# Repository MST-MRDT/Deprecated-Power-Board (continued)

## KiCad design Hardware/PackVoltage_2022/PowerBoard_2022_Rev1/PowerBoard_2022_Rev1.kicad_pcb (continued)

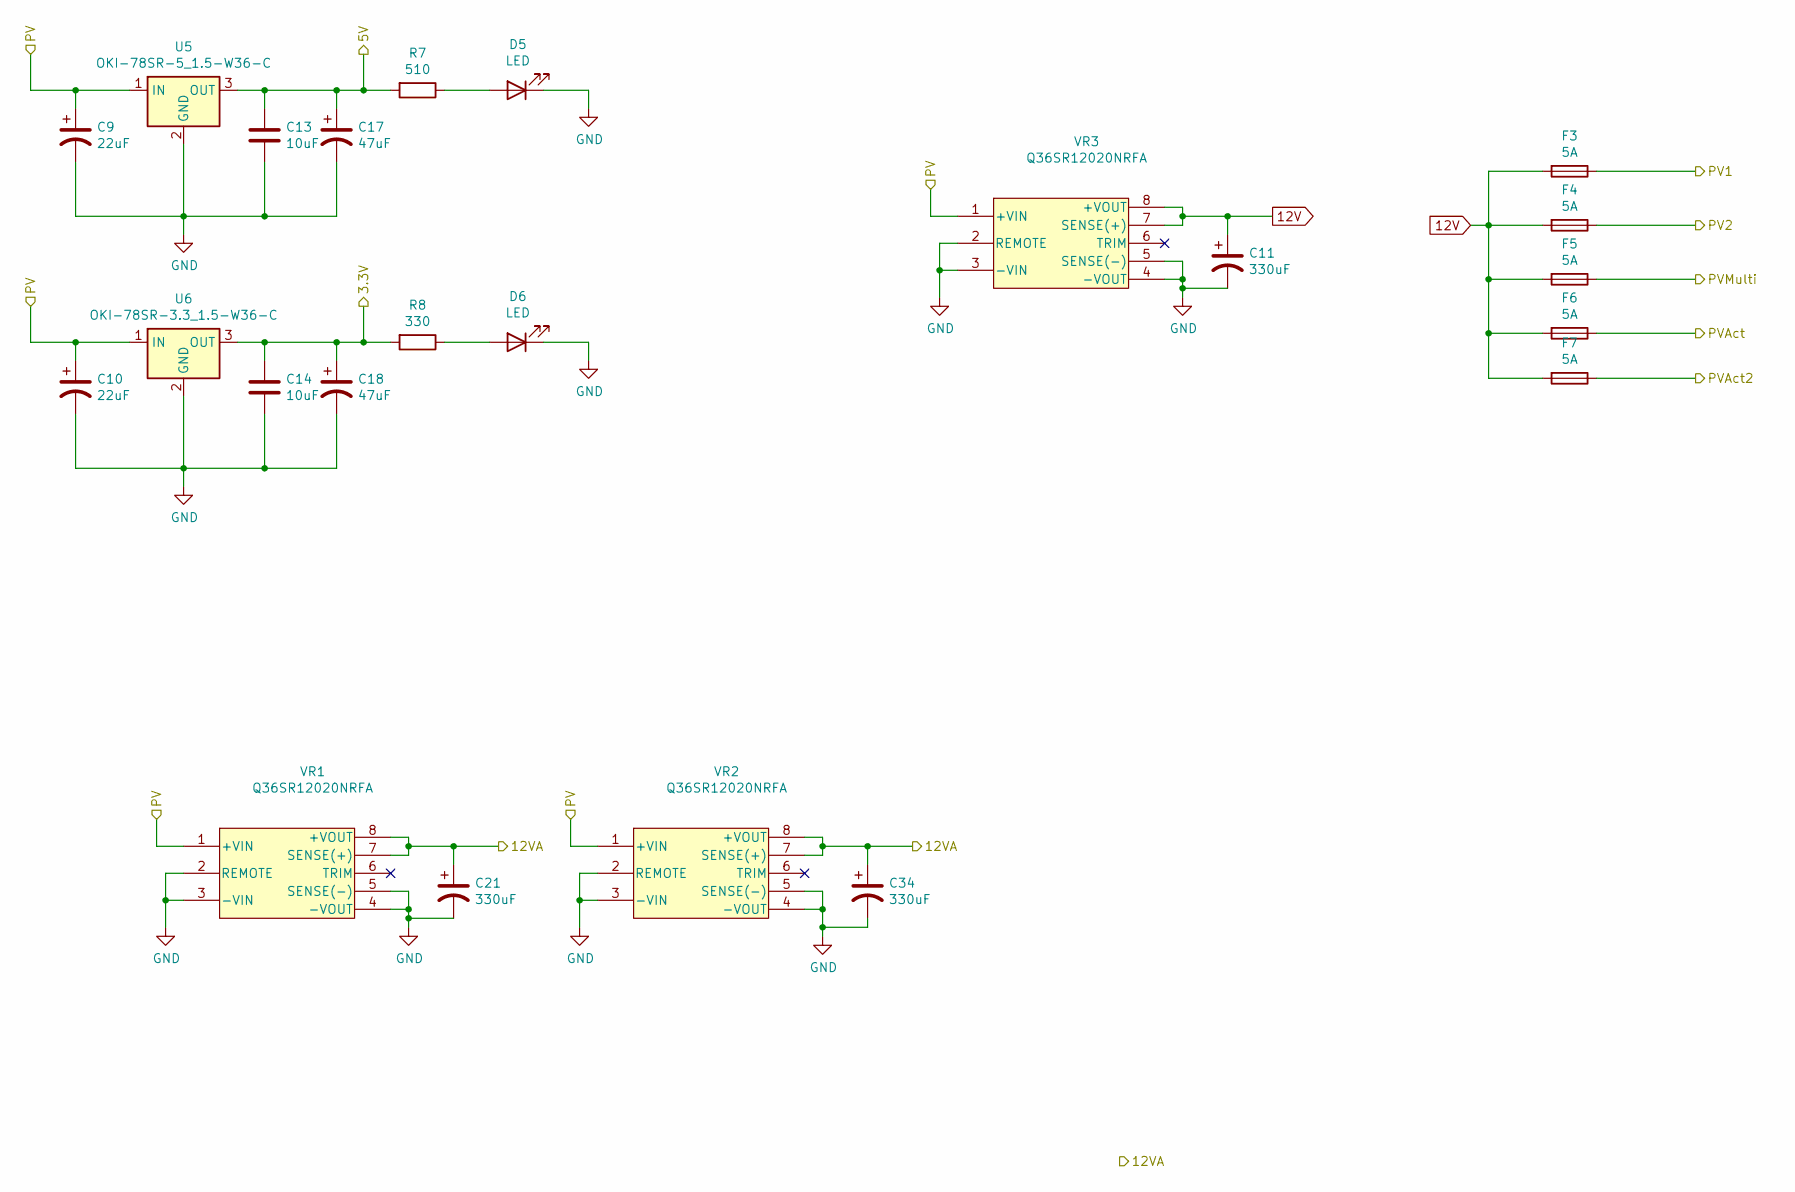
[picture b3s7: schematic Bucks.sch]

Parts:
C9, C10: 22uF; CP_Radial_D6.3mm_P2.50mm
C11, C21, C34: 330uF; CP_Radial_D12.5mm_P5.00mm
C13, C14: 10uF; C_0603_1608Metric_Pad1.05x0.95mm_HandSolder
C17, C18: 47uF; CP_Radial_D6.3mm_P2.50mm
D5, D6: LED; LED_0603_1608Metric_Pad1.05x0.95mm_HandSolder
F3, F4, F5, F6, F7: 5A; ATC_Fuse_Block
R7: 510; R_0603_1608Metric_Pad1.05x0.95mm_HandSolder
R8: 330; R_0603_1608Metric_Pad1.05x0.95mm_HandSolder
U5: OKI-78SR-5_1.5-W36-C; OKI_Horizontal
U6: OKI-78SR-3.3_1.5-W36-C; OKI_Horizontal
VR1, VR2, VR3: Q36SR12020NRFA

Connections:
3.3V: C14.1, C18.1, R8.2, U6.3 (OUT); also elsewhere on the board
5V: C13.1, C17.1, R7.2, U5.3 (OUT); also elsewhere on the board
12V: C11.1, F3.2, F4.2, F5.2, F6.2, F7.2, VR3.7 (SENSE(+)), VR3.8 (+VOUT)
12VA: C21.1, C34.1, VR1.7 (SENSE(+)), VR1.8 (+VOUT), VR2.7 (SENSE(+)), VR2.8 (+VOUT); also elsewhere on the board
GND: C9.2, C10.2, C11.2, C13.2, C14.2, C17.2, C18.2, C21.2, C34.2, D5.1 (K), D6.1 (K), U5.2 (GND), U6.2 (GND), VR1.2 (REMOTE), VR1.3 (-VIN), VR1.4 (-VOUT), VR1.5 (SENSE(-)), VR2.2 (REMOTE), VR2.3 (-VIN), VR2.4 (-VOUT), VR2.5 (SENSE(-)), VR3.2 (REMOTE), VR3.3 (-VIN), VR3.4 (-VOUT), VR3.5 (SENSE(-)); also elsewhere on the board
unnamed: D5.2 (A), R7.1
unnamed: D6.2 (A), R8.1
PV: C9.1, C10.1, U5.1 (IN), U6.1 (IN), VR1.1 (+VIN), VR2.1 (+VIN), VR3.1 (+VIN); also elsewhere on the board
PV1: F3.1; also elsewhere on the board
PV2: F4.1; also elsewhere on the board
PVAct: F6.1; also elsewhere on the board
PVAct2: F7.1; also elsewhere on the board
PVMulti: F5.1; also elsewhere on the board

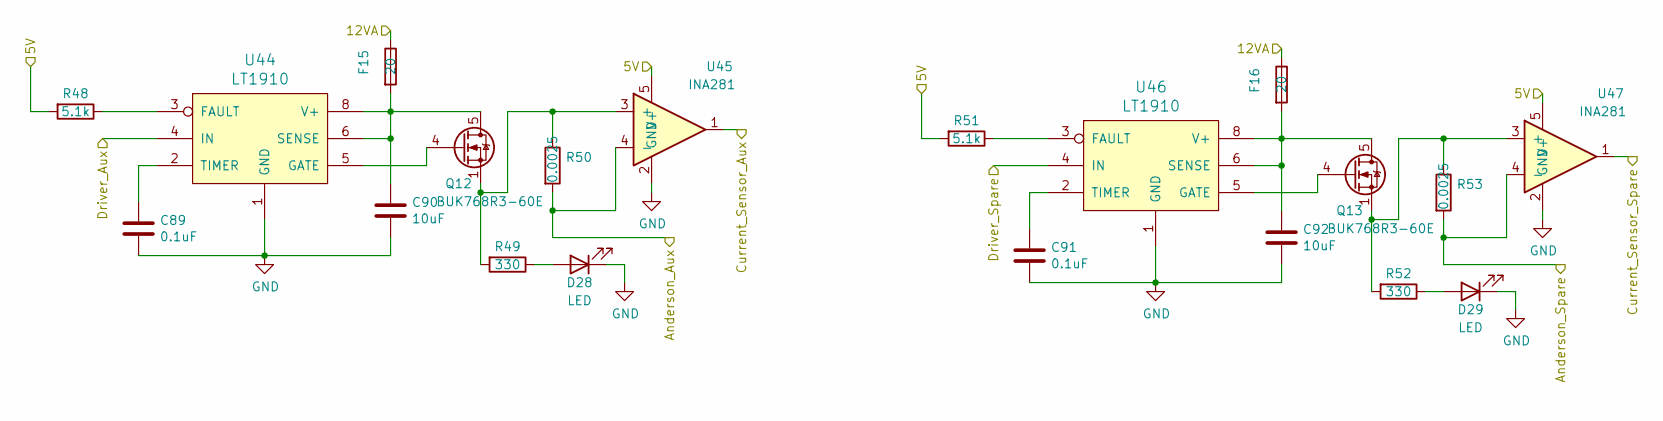
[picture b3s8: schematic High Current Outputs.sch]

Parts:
C89, C91: 0.1uF; C_0603_1608Metric_Pad1.05x0.95mm_HandSolder
C90, C92: 10uF; C_0603_1608Metric_Pad1.05x0.95mm_HandSolder
D28, D29: LED; LED_0603_1608Metric_Pad1.05x0.95mm_HandSolder
F15, F16: 20; ATC_Fuse_Block
Q12, Q13: BUK768R3-60E; LFPAK33
R48, R51: 5.1k; R_0603_1608Metric_Pad1.05x0.95mm_HandSolder
R49, R52: 330; R_0603_1608Metric_Pad1.05x0.95mm_HandSolder
R50, R53: 0.0025; R_0402_1005Metric_Pad0.72x0.64mm_HandSolder
U44, U46: LT1910; SOIC-8_3.9x4.9mm_P1.27mm
U45, U47: INA281; SOT-23-5

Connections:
5V: R48.2, R51.2, U45.5 (V+), U47.5 (V+); also elsewhere on the board
12VA: F15.1, F16.1; also elsewhere on the board
/12V/Current_Sensor_Spare: U47.1
Anderson_Aux_Logic: R50.2, U45.4 (-); also elsewhere on the board
Anderson_Spare: R53.2, U47.4 (-); also elsewhere on the board
Current_Sensor_Aux_Logic: U45.1; also elsewhere on the board
Driver_Aux_Logic: U44.4 (IN); also elsewhere on the board
Driver_Spare: U46.4 (IN); also elsewhere on the board
GND: C89.2, C90.2, C91.2, C92.2, D28.1 (K), D29.1 (K), U44.1 (GND), U45.2 (GND), U46.1 (GND), U47.2 (GND); also elsewhere on the board
unnamed: C89.1, U44.2 (TIMER)
unnamed: C90.1, F15.2, Q12.5 (D), U44.6 (SENSE), U44.8 (V+)
unnamed: C91.1, U46.2 (TIMER)
unnamed: C92.1, F16.2, Q13.5 (D), U46.6 (SENSE), U46.8 (V+)
unnamed: D28.2 (A), R49.1
unnamed: D29.2 (A), R52.1
unnamed: Q12.1 (S), Q12.2 (S), Q12.3 (S), R49.2, R50.1, U45.3 (+)
unnamed: Q12.4 (G), U44.5 (GATE)
unnamed: Q13.1 (S), Q13.2 (S), Q13.3 (S), R52.2, R53.1, U47.3 (+)
unnamed: Q13.4 (G), U46.5 (GATE)
unnamed: R48.1, U44.3 (FAULT)
unnamed: R51.1, U46.3 (FAULT)

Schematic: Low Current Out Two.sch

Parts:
C93, C94, C95, C96, C102, C104, C105, C106, C107: 0.1uF; C_0603_1608Metric_Pad1.05x0.95mm_HandSolder
C97, C98, C99, C100, C101, C103, C108, C109, C110: 10uF; C_0603_1608Metric_Pad1.05x0.95mm_HandSolder
D30, D31, D32, D33, D34, D35, D36, D37, D38: LED; LED_0603_1608Metric_Pad1.05x0.95mm_HandSolder
Q14, Q15, Q16, Q17, Q18, Q19, Q20, Q21, Q22: BUK768R3-60E; LFPAK33
R54, R55, R56, R57, R66, R69, R72, R73, R74: 5.1k; R_0603_1608Metric_Pad1.05x0.95mm_HandSolder
R58, R59, R60, R61, R68, R71, R75, R76, R77: 330; R_0603_1608Metric_Pad1.05x0.95mm_HandSolder
R62, R63, R64, R65, R67, R70, R78, R79, R80: 0.0025; R_2512_6332Metric_Pad1.40x3.35mm_HandSolder
U48, U49, U50, U51, U57, U59, U60, U61, U62: LT1910; SOIC-8_3.9x4.9mm_P1.27mm
U52, U53, U54, U55, U56, U58, U63, U64, U65: INA281; SOT-23-5

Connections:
5V: R54.2, R55.2, R56.2, R57.2, R66.2, R69.2, R72.2, R73.2, R74.2, U52.5 (V+), U53.5 (V+), U54.5 (V+), U55.5 (V+), U56.5 (V+), U58.5 (V+), U63.5 (V+), U64.5 (V+), U65.5 (V+); also elsewhere on the board
Anderson_BBB: R64.2, U54.4 (-); also elsewhere on the board
Anderson_Cam1: R65.2, U55.4 (-); also elsewhere on the board
Anderson_Cam2: R63.2, U53.4 (-); also elsewhere on the board
Anderson_Drive: R67.2, U56.4 (-); also elsewhere on the board
Anderson_Gimbal: R62.2, U52.4 (-); also elsewhere on the board
Anderson_Multimedia: R70.2, U58.4 (-); also elsewhere on the board
Anderson_Nav: R78.2, U63.4 (-); also elsewhere on the board
Anderson_NetSwitch: R79.2, U64.4 (-); also elsewhere on the board
Anderson_SciSensor: R80.2, U65.4 (-); also elsewhere on the board
Current_Sensor_BBB: U54.1; also elsewhere on the board
Current_Sensor_Cam1: U55.1; also elsewhere on the board
Current_Sensor_Cam2: U53.1; also elsewhere on the board
Current_Sensor_Drive: U56.1; also elsewhere on the board
Current_Sensor_Gimbal: U52.1
Current_Sensor_Multimedia: U58.1; also elsewhere on the board
Current_Sensor_Nav: U63.1; also elsewhere on the board
Current_Sensor_NetSwitch: U64.1; also elsewhere on the board
Current_Sensor_SciSensor: U65.1
Driver_BBB: U50.4 (IN); also elsewhere on the board
Driver_Cam1: U51.4 (IN); also elsewhere on the board
Driver_Cam2: U49.4 (IN); also elsewhere on the board
Driver_Drive: U57.4 (IN); also elsewhere on the board
Driver_Gimbal: U48.4 (IN); also elsewhere on the board
Driver_Multimedia: U59.4 (IN); also elsewhere on the board
Driver_Nav: U60.4 (IN); also elsewhere on the board
Driver_NetSwitch: U61.4 (IN); also elsewhere on the board
Driver_SciSensor: U62.4 (IN); also elsewhere on the board
GND: C93.2, C94.2, C95.2, C96.2, C97.2, C98.2, C99.2, C100.2, C101.2, C102.2, C103.2, C104.2, C105.2, C106.2, C107.2, C108.2, C109.2, C110.2, D30.1 (K), D31.1 (K), D32.1 (K), D33.1 (K), D34.1 (K), D35.1 (K), D36.1 (K), D37.1 (K), D38.1 (K), U48.1 (GND), U49.1 (GND), U50.1 (GND), U51.1 (GND), U52.2 (GND), U53.2 (GND), U54.2 (GND), U55.2 (GND), U56.2 (GND), U57.1 (GND), U58.2 (GND), U59.1 (GND), U60.1 (GND), U61.1 (GND), U62.1 (GND), U63.2 (GND), U64.2 (GND), U65.2 (GND); also elsewhere on the board
unnamed: C93.1, U48.2 (TIMER)
unnamed: C94.1, U49.2 (TIMER)
unnamed: C95.1, U50.2 (TIMER)
unnamed: C96.1, U51.2 (TIMER)
unnamed: C102.1, U57.2 (TIMER)
unnamed: C104.1, U59.2 (TIMER)
unnamed: C105.1, U60.2 (TIMER)
unnamed: C106.1, U61.2 (TIMER)
unnamed: C107.1, U62.2 (TIMER)
unnamed: D30.2 (A), R58.1
unnamed: D31.2 (A), R59.1
unnamed: D32.2 (A), R60.1
unnamed: D33.2 (A), R61.1
unnamed: D34.2 (A), R68.1
unnamed: D35.2 (A), R71.1
unnamed: D36.2 (A), R75.1
unnamed: D37.2 (A), R76.1
unnamed: D38.2 (A), R77.1
unnamed: Q14.1 (S), Q14.2 (S), Q14.3 (S), R58.2, R62.1, U52.3 (+)
unnamed: Q14.4 (G), U48.5 (GATE)
unnamed: Q15.1 (S), Q15.2 (S), Q15.3 (S), R59.2, R63.1, U53.3 (+)
unnamed: Q15.4 (G), U49.5 (GATE)
unnamed: Q16.1 (S), Q16.2 (S), Q16.3 (S), R60.2, R64.1, U54.3 (+)
unnamed: Q16.4 (G), U50.5 (GATE)
unnamed: Q17.1 (S), Q17.2 (S), Q17.3 (S), R61.2, R65.1, U55.3 (+)
unnamed: Q17.4 (G), U51.5 (GATE)
unnamed: Q18.1 (S), Q18.2 (S), Q18.3 (S), R67.1, R68.2, U56.3 (+)
unnamed: Q18.4 (G), U57.5 (GATE)
unnamed: Q19.1 (S), Q19.2 (S), Q19.3 (S), R70.1, R71.2, U58.3 (+)
unnamed: Q19.4 (G), U59.5 (GATE)
unnamed: Q20.1 (S), Q20.2 (S), Q20.3 (S), R75.2, R78.1, U63.3 (+)
unnamed: Q20.4 (G), U60.5 (GATE)
unnamed: Q21.1 (S), Q21.2 (S), Q21.3 (S), R76.2, R79.1, U64.3 (+)
unnamed: Q21.4 (G), U61.5 (GATE)
unnamed: Q22.1 (S), Q22.2 (S), Q22.3 (S), R77.2, R80.1, U65.3 (+)
unnamed: Q22.4 (G), U62.5 (GATE)
unnamed: R54.1, U48.3 (FAULT)
unnamed: R55.1, U49.3 (FAULT)
unnamed: R56.1, U50.3 (FAULT)
unnamed: R57.1, U51.3 (FAULT)
unnamed: R66.1, U57.3 (FAULT)
unnamed: R69.1, U59.3 (FAULT)
unnamed: R72.1, U60.3 (FAULT)
unnamed: R73.1, U61.3 (FAULT)
unnamed: R74.1, U62.3 (FAULT)
PV1: C98.1, C99.1, C100.1, C108.1, Q15.5 (D), Q16.5 (D), Q17.5 (D), Q20.5 (D), U49.6 (SENSE), U49.8 (V+), U50.6 (SENSE), U50.8 (V+), U51.6 (SENSE), U51.8 (V+), U60.6 (SENSE), U60.8 (V+); also elsewhere on the board
PV2: C97.1, C101.1, C109.1, C110.1, Q14.5 (D), Q18.5 (D), Q21.5 (D), Q22.5 (D), U48.6 (SENSE), U48.8 (V+), U57.6 (SENSE), U57.8 (V+), U61.6 (SENSE), U61.8 (V+), U62.6 (SENSE), U62.8 (V+); also elsewhere on the board
PVMulti: C103.1, Q19.5 (D), U59.6 (SENSE), U59.8 (V+); also elsewhere on the board

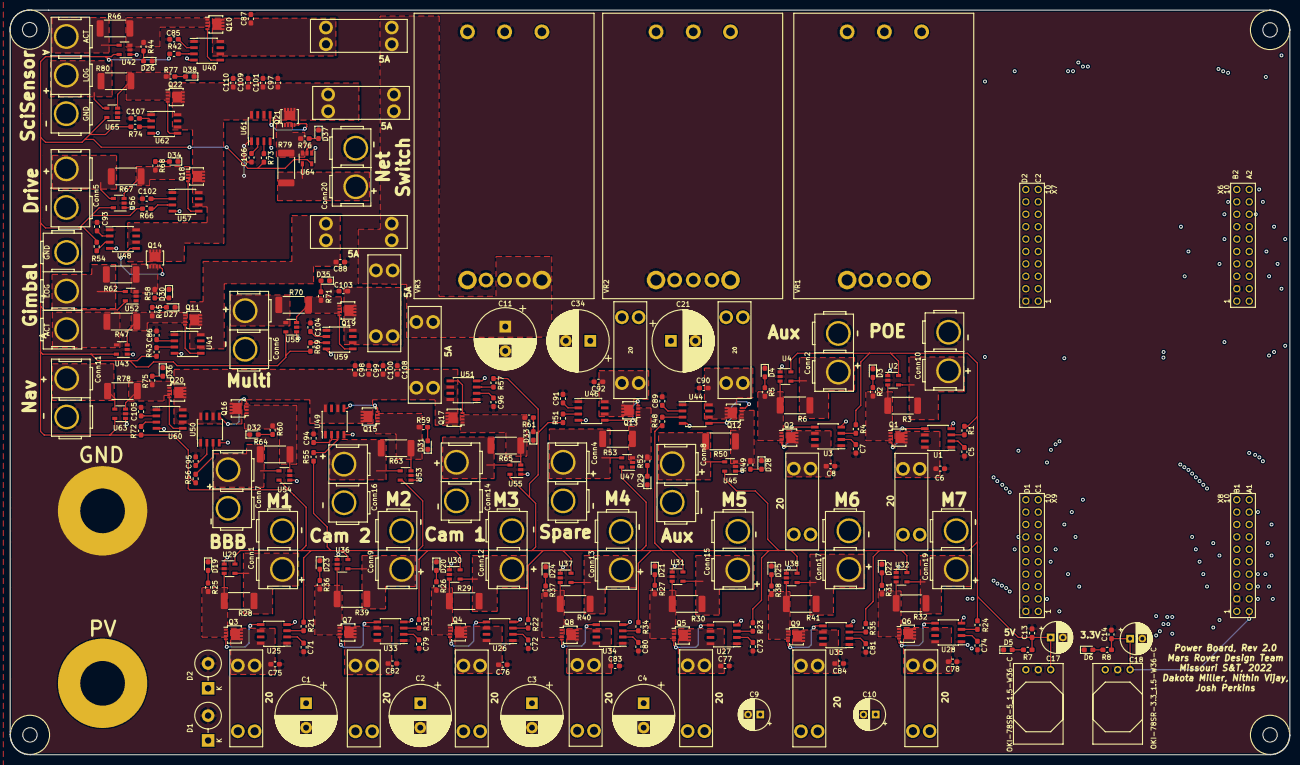
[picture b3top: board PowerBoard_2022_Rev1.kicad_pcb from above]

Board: 4 copper layers, 261.9 x 152.4 mm, 261 parts (0 on the bottom side), 197 nets.

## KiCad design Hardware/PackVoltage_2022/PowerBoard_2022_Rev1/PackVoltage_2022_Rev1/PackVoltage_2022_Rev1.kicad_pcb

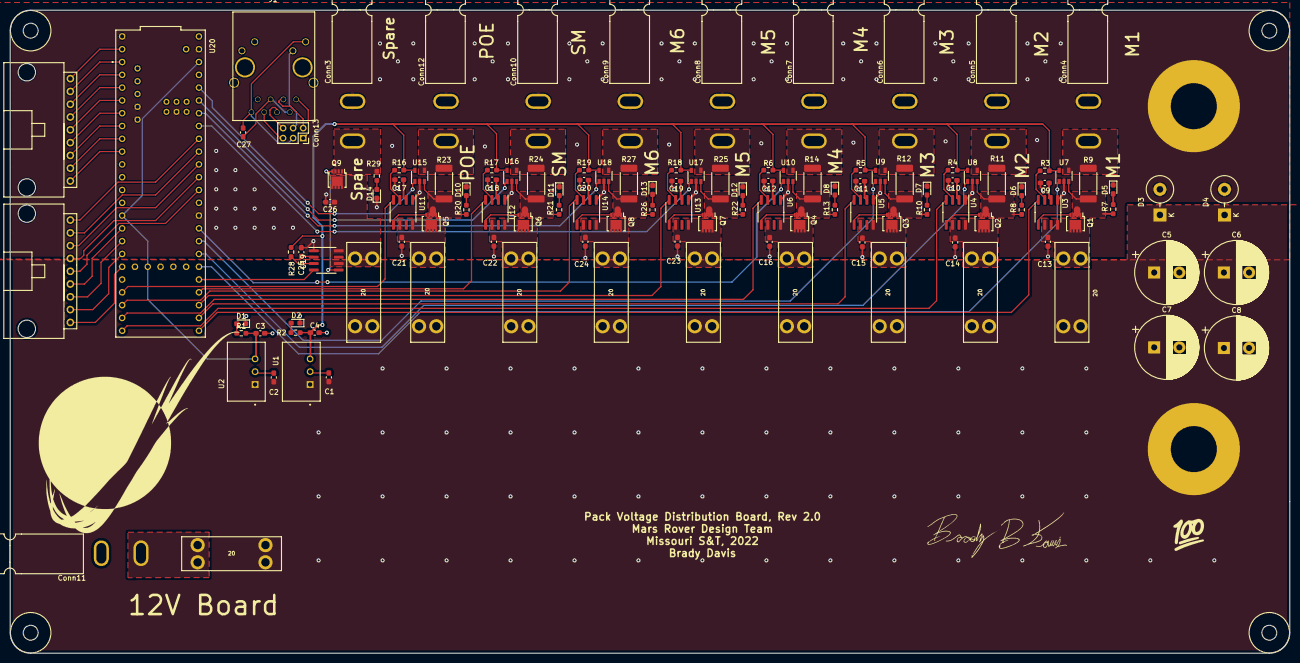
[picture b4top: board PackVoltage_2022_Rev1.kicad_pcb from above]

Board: 2 copper layers, 254.0 x 127.6 mm, 123 parts (0 on the bottom side), 111 nets.

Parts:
C1, C2, C13, C14, C15, C16, C21, C22, C23, C24, C26: 10uF; C_0603_1608Metric_Pad1.08x0.95mm_HandSolder
C3, C4: 22uF; C_0603_1608Metric_Pad1.08x0.95mm_HandSolder
C5, C6, C7, C8: 470uF; CP_Radial_D12.5mm_P5.00mm
C9, C10, C11, C12, C17, C18, C19, C20, C25: 0.1uF; C_0603_1608Metric_Pad1.08x0.95mm_HandSolder
C27: 0.1 uF; C_0603_1608Metric_Pad1.08x0.95mm_HandSolder
Conn1, Conn2: Molex_SL_10; MOLEX_SL_09_Horizontal
Conn3: Spare; Square_Anderson_2_H_Stacked_PV
Conn4: M1; Square_Anderson_2_H_Stacked_PV
Conn5: M2; Square_Anderson_2_H_Stacked_PV
Conn6: M3; Square_Anderson_2_H_Stacked_PV
Conn7: M4; Square_Anderson_2_H_Stacked_PV
Conn8: M5; Square_Anderson_2_H_Stacked_PV
Conn9: M6; Square_Anderson_2_H_Stacked_PV
Conn10: SpareMotor; Square_Anderson_2_H_Stacked_PV
Conn11: 12V; Square_Anderson_2_H_Stacked_PV
Conn12: POE; Square_Anderson_2_H_Stacked_PV
Conn13: Molex_uF_D_06; PinSocket_2x03_P2.00mm_Vertical
D1, D2, D5, D6, D7, D8, D10, D11, D12, D13, D14: LED; LED_0603_1608Metric_Pad1.05x0.95mm_HandSolder
D3, D4: 1.5KE36A+; D_DO-201_P5.08mm_Vertical_KathodeUp
F1, F2, F3, F4, F5, F6, F7, F8, F9, F10: 20; ATC_Fuse_Block
GND1: Via; BATT_PWR_VIA
J1: RJ45_LED_Shielded; RJ45_Teensy
Q1, Q2, Q3, Q4, Q5, Q6, Q7, Q8, Q9: BUK7S2R0-40HJ; LFPAK33
R1: 130; R_0603_1608Metric_Pad0.98x0.95mm_HandSolder
R2: 300; R_0603_1608Metric_Pad0.98x0.95mm_HandSolder
R3, R4, R5, R6, R16, R17, R18, R19, R28: 5.1k; R_0603_1608Metric_Pad0.98x0.95mm_HandSolder
R7, R8, R10, R13, R20, R21, R22, R26, R29: 2800; R_0603_1608Metric_Pad0.98x0.95mm_HandSolder
R9, R11, R12, R14, R23, R24, R25, R27: .0015; R_2512_6332Metric_Pad1.40x3.35mm_HandSolder
U1, U2: TSR1-2433; TSR_1-2433
U3, U4, U5, U6, U11, U12, U13, U14, U19: LT1910; SOIC-8_3.9x4.9mm_P1.27mm
U7, U8, U9, U10, U15, U16, U17, U18: INA281; SOT-23-5
U20: Teensy4.1_DEV-16771; MODULE_DEV-16771
V1: BATT_PWR_VIA

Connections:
+3V3: C3.1, R1.2, U2.3, U20.3.3V_1, U20.3.3V_2, U20.3.3V_3
+5V: C4.1, R2.2, R3.2, R4.2, R5.2, R6.2, R16.2, R17.2, R18.2, R19.2, R28.2, U1.3, U7.5, U8.5, U9.5, U10.5, U15.5, U16.5, U17.5, U18.5
/MOTORS/12V: Conn11.1, F5.1
/MOTORS/Anderson_M1: Conn4.1, R9.2, U7.4
/MOTORS/Anderson_M2: Conn5.1, R11.2, U8.4
/MOTORS/Anderson_M3: Conn6.1, R12.2, U9.4
/MOTORS/Anderson_M4: Conn7.1, R14.2, U10.4
/MOTORS/Anderson_M5: Conn8.1, R25.2, U17.4
/MOTORS/Anderson_M6: Conn9.1, R27.2, U18.4
/MOTORS/Anderson_POE: Conn12.1, R23.2, U15.4
/MOTORS/Anderson_Spare: Conn3.1, Q9.1, Q9.2, Q9.3, R29.2
/MOTORS/Anderson_SpareMotor: Conn10.1, R24.2, U16.4
Current_Sensor_12VSpare: Conn2.1, U20.27
Current_Sensor_Aux: Conn2.9, U20.18
Current_Sensor_BBB: Conn2.8, U20.17
Current_Sensor_Cam1: Conn2.7, U20.16
Current_Sensor_Cam2: Conn2.6, U20.15
Current_Sensor_Drive: Conn2.5, U20.14
Current_Sensor_Gim: Conn2.4, U20.24
Current_Sensor_M1: U7.1, U20.38
Current_Sensor_M2: U8.1, U20.39
Current_Sensor_M3: U9.1, U20.40
Current_Sensor_M4: U10.1, U20.41
Current_Sensor_M5: U17.1, U20.19
Current_Sensor_M6: U18.1, U20.20
Current_Sensor_Multi: Conn2.3, U20.25
Current_Sensor_Nav: Conn2.2, U20.26
Current_Sensor_POE: U15.1, U20.22
Current_Sensor_SpareMotor: U16.1, U20.21
Driver_12VSpare: Conn1.9, U20.0
Driver_Aux: Conn1.1, U20.8
Driver_BBB: Conn1.2, U20.7
Driver_Cam1: Conn1.3, U20.6
Driver_Cam2: Conn1.4, U20.5
Driver_Drive: Conn1.5, U20.4
Driver_Gim: Conn1.6, U20.3
Driver_M1: U3.4, U20.33
Driver_M2: U4.4, U20.32
Driver_M3: U5.4, U20.34
Driver_M4: U6.4, U20.31
Driver_M5: U13.4, U20.35
Driver_M6: U14.4, U20.30
Driver_Multi: Conn1.7, U20.2
Driver_Nav: Conn1.8, U20.1
Driver_POE: U11.4, U20.29
Driver_Spare: U19.4, U20.37
Driver_SpareMotor: U12.4, U20.36
GND: C1.2, C2.2, C3.2, C4.2, C5.2, C6.2, C7.2, C8.2, C9.2, C10.2, C11.2, C12.2, C13.2, C14.2, C15.2, C16.2, C17.2, C18.2, C19.2, C20.2, C21.2, C22.2, C23.2, C24.2, C25.2, C26.2, Conn3.2, Conn4.2, Conn5.2, Conn6.2, Conn7.2, Conn8.2, Conn9.2, Conn10.2, Conn11.2, Conn12.2, D1.1, D2.1, D3.2, D4.2, D5.1, D6.1, D7.1, D8.1, D10.1, D11.1, D12.1, D13.1, D14.1, GND1.1, J1.SH, U1.2, U2.2, U3.1, U4.1, U5.1, U6.1, U7.2, U8.2, U9.2, U10.2, U11.1, U12.1, U13.1, U14.1, U15.2, U16.2, U17.2, U18.2, U19.1, U20.GND1, U20.GND2, U20.GND3, U20.GND4, U20.GND5, U20.USB_GND1, U20.USB_GND2
unnamed: C9.1, U3.2
unnamed: C10.1, U4.2
unnamed: C11.1, U5.2
unnamed: C12.1, U6.2
unnamed: C13.1, F1.2, Q1.5, U3.6, U3.8
unnamed: C14.1, F2.2, Q2.5, U4.6, U4.8
unnamed: C15.1, F3.2, Q3.5, U5.6, U5.8
unnamed: C16.1, F4.2, Q4.5, U6.6, U6.8
unnamed: C17.1, U11.2
unnamed: C18.1, U12.2
unnamed: C19.1, U13.2
unnamed: C20.1, U14.2
unnamed: C21.1, F6.2, Q5.5, U11.6, U11.8
unnamed: C22.1, F7.2, Q6.5, U12.6, U12.8
unnamed: C23.1, F8.2, Q7.5, U13.6, U13.8
unnamed: C24.1, F9.2, Q8.5, U14.6, U14.8
unnamed: C25.1, U19.2
unnamed: C26.1, F10.2, Q9.5, U19.6, U19.8
unnamed: C27.1, J1.2, J1.5
unnamed: C27.2, Conn13.3, J1.8, J1.9
unnamed: Conn13.1, J1.1
unnamed: Conn13.2, J1.3
unnamed: Conn13.4, J1.10
unnamed: Conn13.5, J1.6
unnamed: Conn13.6, J1.4
unnamed: D1.2, R1.1
unnamed: D2.2, R2.1
unnamed: D5.2, R7.1
unnamed: D6.2, R8.1
unnamed: D7.2, R10.1
unnamed: D8.2, R13.1
unnamed: D10.2, R20.1
unnamed: D11.2, R21.1
unnamed: D12.2, R22.1
unnamed: D13.2, R26.1
unnamed: D14.2, R29.1
unnamed: Q1.1, Q1.2, Q1.3, R7.2, R9.1, U7.3
unnamed: Q1.4, U3.5
unnamed: Q2.1, Q2.2, Q2.3, R8.2, R11.1, U8.3
unnamed: Q2.4, U4.5
unnamed: Q3.1, Q3.2, Q3.3, R10.2, R12.1, U9.3
unnamed: Q3.4, U5.5
unnamed: Q4.1, Q4.2, Q4.3, R13.2, R14.1, U10.3
unnamed: Q4.4, U6.5
unnamed: Q5.1, Q5.2, Q5.3, R20.2, R23.1, U15.3
unnamed: Q5.4, U11.5
unnamed: Q6.1, Q6.2, Q6.3, R21.2, R24.1, U16.3
unnamed: Q6.4, U12.5
unnamed: Q7.1, Q7.2, Q7.3, R22.2, R25.1, U17.3
unnamed: Q7.4, U13.5
unnamed: Q8.1, Q8.2, Q8.3, R26.2, R27.1, U18.3
unnamed: Q8.4, U14.5
unnamed: Q9.4, U19.5
unnamed: R3.1, U3.3
unnamed: R4.1, U4.3
unnamed: R5.1, U5.3
unnamed: R6.1, U6.3
unnamed: R16.1, U11.3
unnamed: R17.1, U12.3
unnamed: R18.1, U13.3
unnamed: R19.1, U14.3
unnamed: R28.1, U19.3
PV: C1.1, C2.1, C5.1, C6.1, C7.1, C8.1, D3.1, D4.1, F1.1, F2.1, F3.1, F4.1, F5.2, F6.1, F7.1, F8.1, F9.1, F10.1, U1.1, U2.1, V1.1

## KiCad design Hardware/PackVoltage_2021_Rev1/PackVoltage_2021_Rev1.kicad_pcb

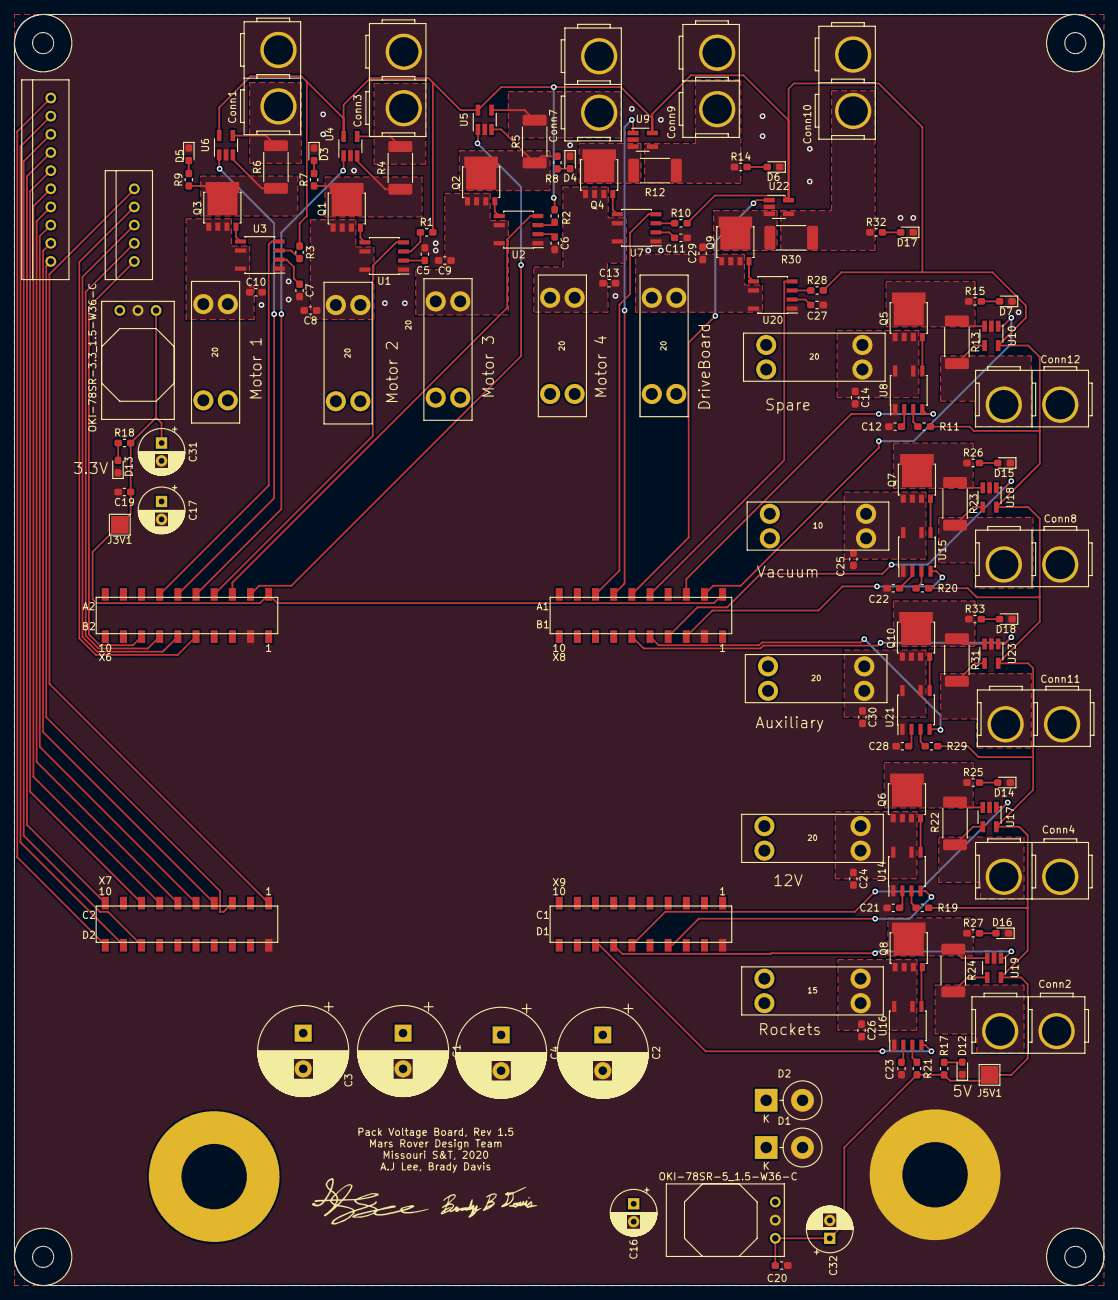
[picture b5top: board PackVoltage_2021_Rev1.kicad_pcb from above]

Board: 2 copper layers, 152.4 x 177.8 mm, 135 parts (0 on the bottom side), 111 nets.

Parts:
C1, C2, C3, C4: 470uF; CP_Radial_D12.5mm_P5.00mm
C5, C6, C7, C11, C12, C21, C22, C23, C27, C28: 0.1uF; C_0603_1608Metric_Pad1.05x0.95mm_HandSolder
C8, C9, C10, C13, C14, C19, C20, C24, C25, C26, C29, C30: 10uF; C_0603_1608Metric_Pad1.05x0.95mm_HandSolder
C16, C17: 22uF; CP_Radial_D6.3mm_P2.50mm
C31, C32: 47uF; CP_Radial_D6.3mm_P2.50mm
Conn1: Motor 1; Anderson_2_Vertical_Sidy_by_Side
Conn2: Rockets; Anderson_2_Vertical_Sidy_by_Side
Conn3: Motor 2; Anderson_2_Vertical_Sidy_by_Side
Conn4: 12 V; Anderson_2_Vertical_Sidy_by_Side
Conn5: Molex_SL_10; MOLEX_SL_10_Vertical
Conn6: Molex_SL_05; MOLEX_SL_05_Vertical
Conn7: Motor 3; Anderson_2_Vertical_Sidy_by_Side
Conn8: Vaccum; Anderson_2_Vertical_Sidy_by_Side
Conn9: Motor 4; Anderson_2_Vertical_Sidy_by_Side
Conn10: Driveboard; Anderson_2_Vertical_Sidy_by_Side
Conn11: Auxiliary; Anderson_2_Vertical_Sidy_by_Side
Conn12: Spare; Anderson_2_Vertical_Sidy_by_Side
D1, D2: 1.5KE36A+; D_DO-201AD_P5.08mm_Vertical_KathodeUp
D3, D4, D5, D6, D7, D12, D13, D14, D15, D16, D17, D18: LED; LED_0603_1608Metric_Pad1.05x0.95mm_HandSolder
F1, F2, F3, F4, F5, F6, F9, F10: 20; ATC_Fuse_Block
F7: 10; ATC_Fuse_Block
F8: 15; ATC_Fuse_Block
GND1: Via; BATT_PWR_VIA
J3V1, J5V1: Test_Point; TestPoint_Pad_2.5x2.5mm
Q1, Q2, Q3, Q4, Q5, Q6, Q7, Q8, Q9, Q10: PSMN025-80YL; LFPAK56_MOSFET
R1, R2, R3, R10, R11, R19, R20, R21, R28, R29: 5.1k; R_0603_1608Metric_Pad1.05x0.95mm_HandSolder
R4, R5, R6, R12, R13, R22, R23, R24, R30, R31: 0.0025; R_2512_6332Metric_Pad1.52x3.35mm_HandSolder
R7, R8, R9, R14, R15, R26, R27, R32, R33: 3300; R_0603_1608Metric_Pad1.05x0.95mm_HandSolder
R17: 510; R_0603_1608Metric_Pad1.05x0.95mm_HandSolder
R18: 330; R_0603_1608Metric_Pad1.05x0.95mm_HandSolder
R25: 1200; R_0603_1608Metric_Pad1.05x0.95mm_HandSolder
U1, U2, U3, U7, U8, U14, U15, U16, U20, U21: LT1910; SOIC-8-N7_3.9x4.9mm_P1.27mm
U4, U5, U6, U9, U10, U17, U18, U19, U22, U23: INA281; SOT-23-5_HandSoldering
U12: OKI-78SR-3.3_1.5-W36-C; OKI_Horizontal
U13: OKI-78SR-5_1.5-W36-C; OKI_Horizontal
U24: TM4C129E_Launchpad; TM4C129E_Launchpad_FULL_SMD_TOP
V1: BATT_PWR_VIA

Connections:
+3V3: C19.1, C31.1, J3V1.1, R18.2, U12.3, U24.+3V3, U24.+3V3'
+5V: C20.1, C32.1, J5V1.1, R1.2, R2.2, R3.2, R10.2, R11.2, R17.2, R19.2, R20.2, R21.2, R28.2, R29.2, U4.5, U5.5, U6.5, U9.5, U10.5, U13.3, U17.5, U18.5, U19.5, U22.5, U23.5
/Anderson_A1: Conn11.2, R31.2, U23.4
/Anderson_D1: Conn10.2, R30.2, R32.1, U22.4
/Anderson_M1: Conn1.2, R6.2, U6.4
/Anderson_M2: Conn3.2, R4.2, U4.4
/Anderson_M3: Conn7.2, R5.2, U5.4
/Anderson_M4: Conn9.2, R12.2, R14.1, U9.4
/Anderson_R1: Conn2.2, R24.2, U19.4
/Anderson_S1: Conn12.2, R13.2, U10.4
/Anderson_T1: Conn4.2, R22.2, U17.4
/Anderson_V1: Conn8.2, R23.2, U18.4
/AuxActCTL: Conn5.4, U24.PM2
/AuxLogCTL: Conn5.3, U24.PM1
/AuxMountSense: Conn6.1, U24.PK3
/BuckCTL: Conn6.5, U24.PG1
/CameraCTL: Conn5.8, U24.PP3
/Current_Sensor_A1: U23.1, U24.PE3
/Current_Sensor_D1: U22.1, U24.PE5
/Current_Sensor_M1: U6.1, U24.PD5
/Current_Sensor_M2: U4.1, U24.PD4
/Current_Sensor_M3: U5.1, U24.PD2
/Current_Sensor_M4: U9.1, U24.PD3
/Current_Sensor_R1: U19.1, U24.PD0
/Current_Sensor_S1: U10.1, U24.PE4
/Current_Sensor_T1: U17.1, U24.PD1
/Current_Sensor_V1: U18.1, U24.PE1
/DriveCTL: Conn5.10, U24.PM6
/Driver_A1: U21.4, U24.PE2
/Driver_D1: U20.4, U24.PC6
/Driver_M1: U3.4, U24.PQ0
/Driver_M2: U1.4, U24.PP1
/Driver_M3: U2.4, U24.PP0
/Driver_M4: U7.4, U24.PC7
/Driver_R1: U16.4, U24.PN2
/Driver_S1: U8.4, U24.PC4
/Driver_T1: U14.4, U24.PH3
/Driver_V1: U15.4, U24.PE0
/ExtraCTL: Conn5.9, U24.PQ1
/GimbalActCTL: Conn5.6, U24.PH1
/GimbalLogCTL: Conn5.5, U24.PH0
/GimbalSense: Conn6.4, U24.PK0
/LowCurrentSense: Conn6.3, U24.PK1
/MultimediaActCTL: Conn5.2, U24.PM0
/MultimediaLogCTL: Conn5.1, U24.PK5
/MultimediaSense: Conn6.2, U24.PK2
/NavBoardCTL: Conn5.7, U24.PK7
/PV: C1.1, C2.1, C3.1, C4.1, C16.1, C17.1, D1.1, D2.1, F1.1, F2.1, F3.1, F4.1, F5.1, F6.1, F7.1, F8.1, F9.1, F10.1, U12.1, U13.1, V1.1
GND: C1.2, C2.2, C3.2, C4.2, C5.2, C6.2, C7.2, C8.2, C9.2, C10.2, C11.2, C12.2, C13.2, C14.2, C16.2, C17.2, C19.2, C20.2, C21.2, C22.2, C23.2, C24.2, C25.2, C26.2, C27.2, C28.2, C29.2, C30.2, C31.2, C32.2, Conn1.1, Conn2.1, Conn3.1, Conn4.1, Conn7.1, Conn8.1, Conn9.1, Conn10.1, Conn11.1, Conn12.1, D1.2, D2.2, D3.1, D4.1, D5.1, D6.1, D7.1, D12.1, D13.1, D14.1, D15.1, D16.1, D17.1, D18.1, GND1.1, U1.1, U2.1, U3.1, U4.2, U5.2, U6.2, U7.1, U8.1, U9.2, U10.2, U12.2, U13.2, U14.1, U15.1, U16.1, U17.2, U18.2, U19.2, U20.1, U21.1, U22.2, U23.2, U24.GND
unnamed: C5.1, U1.2
unnamed: C6.1, U2.2
unnamed: C7.1, U3.2
unnamed: C8.1, F1.2, Q1.1, U1.6, U1.8
unnamed: C9.1, F2.2, Q2.1, U2.6, U2.8
unnamed: C10.1, F3.2, Q3.1, U3.6, U3.8
unnamed: C11.1, U7.2
unnamed: C12.1, U8.2
unnamed: C13.1, F4.2, Q4.1, U7.6, U7.8
unnamed: C14.1, F5.2, Q5.1, U8.6, U8.8
unnamed: C21.1, U14.2
unnamed: C22.1, U15.2
unnamed: C23.1, U16.2
unnamed: C24.1, F6.2, Q6.1, U14.6, U14.8
unnamed: C25.1, F7.2, Q7.1, U15.6, U15.8
unnamed: C26.1, F8.2, Q8.1, U16.6, U16.8
unnamed: C27.1, U20.2
unnamed: C28.1, U21.2
unnamed: C29.1, F9.2, Q9.1, U20.6, U20.8
unnamed: C30.1, F10.2, Q10.1, U21.6, U21.8
unnamed: D3.2, R7.2
unnamed: D4.2, R8.2
unnamed: D5.2, R9.2
unnamed: D6.2, R14.2
unnamed: D7.2, R15.2
unnamed: D12.2, R17.1
unnamed: D13.2, R18.1
unnamed: D14.2, R25.2
unnamed: D15.2, R26.2
unnamed: D16.2, R27.2
unnamed: D17.2, R32.2
unnamed: D18.2, R33.2
unnamed: Q1.2, U1.5
unnamed: Q1.3, R4.1, R7.1, U4.3
unnamed: Q2.2, U2.5
unnamed: Q2.3, R5.1, R8.1, U5.3
unnamed: Q3.2, U3.5
unnamed: Q3.3, R6.1, R9.1, U6.3
unnamed: Q4.2, U7.5
unnamed: Q4.3, R12.1, U9.3
unnamed: Q5.2, U8.5
unnamed: Q5.3, R13.1, R15.1, U10.3
unnamed: Q6.2, U14.5
unnamed: Q6.3, R22.1, R25.1, U17.3
unnamed: Q7.2, U15.5
unnamed: Q7.3, R23.1, R26.1, U18.3
unnamed: Q8.2, U16.5
unnamed: Q8.3, R24.1, R27.1, U19.3
unnamed: Q9.2, U20.5
unnamed: Q9.3, R30.1, U22.3
unnamed: Q10.2, U21.5
unnamed: Q10.3, R31.1, R33.1, U23.3
unnamed: R1.1, U1.3
unnamed: R2.1, U2.3
unnamed: R3.1, U3.3
unnamed: R10.1, U7.3
unnamed: R11.1, U8.3
unnamed: R19.1, U14.3
unnamed: R20.1, U15.3
unnamed: R21.1, U16.3
unnamed: R28.1, U20.3
unnamed: R29.1, U21.3

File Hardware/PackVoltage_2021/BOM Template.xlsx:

Id | Designator | Package | Designation | Item Name | Part Number | Vendor | Quantity | Cost Per Item | Cost | URL
1 | F10,F6,F4,F2,F1,F3,F5,F9 | ATC_Fuse_Block | 20 | CL10A106MQ8NNNC | 1276-1119-1-ND | Digikey | 8 | 0.11 | 0.88 | https://www.digikey.com/product-detail/en/samsung-electro-me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
2 | REF**,REF**,REF**,REF** | 4_40_Hole_Corner | 4_40_Hole | Anderson Power 1336G1 Printed Circuit Board High Power 45 Amp Horizontal Bottom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 | 1336G1 | Powerwerx | 4 | 0.55000000000000004 | 2.2000000000000002 | https://powerwerx.com/anderson-1336g1-printed-circuit-board-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
3 | U24 | TM4C129E_Launchpad_FULL_SMD_TOP | TM4C129E_Launchpad | 1327G6-BK Anderson Power Products PP15/30/45 Powerpole Connector Colored Housin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 | 1327G6 | Powerwerx | 1 | 0.37 | 0.37 | https://powerwerx.com/anderson-powerpole-colored-housings
4 | U13 | OKI_Horizontal | OKI-78SR-5_1.5-W36-C | 1327-BK Anderson Power Products PP15/30/45 Powerpole Connector Colored Housing,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 | 1327 | Powerwerx | 1 | 0.37 | 0.37 | https://powerwerx.com/anderson-powerpole-colored-housings
5 | U12 | OKI_Horizontal | OKI-78SR-3.3_1.5-W36-C | 1327G16-BK Anderson Power Products PP15/30/45 Powerpole Connector Colored Housi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 | 1327G16 | Powerwerx | 1 | 0.39 | 0.39 | https://powerwerx.com/anderson-powerpole-colored-housings
6 | Conn6 | MOLEX_SL_04_Horizontal | Molex_SL_04 | 705530002 | WM4901-ND | Digikey | 1 | 0.88 | 0.88 | https://www.digikey.com/products/en?keywords=WM4901-ND
7 | Conn5 | MOLEX_SL_10_Horizontal | Molex_SL_10 | SDZT15R5.6 | SDZT15R5.6CT-ND | Digikey | 1 | 0.25 | 0.25 | https://www.digikey.com/en/products/detail/rohm-semiconducto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
8 | C32,C31 | CP_Radial_D6.3mm_P2.50mm | 47uF | LTST-C191TBKT | 160-1647-1-ND | Digikey | 2 | 0.26200000000000001 | 0.52400000000000002 | https://www.digikey.com/en/products/detail/lite-on-inc/LTST-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
9 | C20,C19,C14,C24,C25,C26,C30,C13,C9,C8,C10,C29 | C_0603_1608Metric_Pad1.05x0.95mm_HandSolder | 10uF | LTST-C191KFKT | 160-1445-1-ND | Digikey | 12 | 0.24 | 2.88 | https://www.digikey.com/en/products/detail/lite-on-inc/LTST-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
10 | C17,C16 | CP_Radial_D6.3mm_P2.50mm | 22uF | LTST-C191KGKT | 160-1446-1-ND | Digikey | 2 | 0.26 | 0.52 | https://www.digikey.com/product-detail/en/lite-on-inc/LTST-C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
11 | U23,U19,U18,U17,U5,U4,U6,U9,U10,U22 | SOT-23-5_HandSoldering | INA281 | EK-TM4C129EXL | 296-44249-ND | Digikey | 10 | 29.99 | 299.89999999999998 | https://www.digikey.com/product-detail/en/texas-instruments/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
12 | U14,U15,U16,U21,U2,U1,U3,U7,U8,U20 | SOIC-8-N7_3.9x4.9mm_P1.27mm | LT1910 | 2N7002AQ-7 | 2N7002AQ-7DICT-ND | Digikey | 10 | 0.28000000000000003 | 2.8000000000000003 | https://www.digikey.com/en/products/detail/diodes-incorporat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
13 | R31,R24,R23,R22,R13,R12,R5,R4,R6,R30 | TO-263-2_TabPin1 | 0.05 | CRCW0603330RFKEBC | CRCW0603330RFKEBCCT-ND | Digikey | 10 | 3.1E-2 | 0.31 | https://www.digikey.com/en/products/detail/vishay-dale/CRCW0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
14 | R15,R7,R9,R14,R26,R27,R33,R8,R32 | R_0603_1608Metric_Pad1.05x0.95mm_HandSolder | 3300 | ESR03EZPJ511 | RHM510DCT-ND | Digikey | 9 | 0.1 | 0.9 | https://www.digikey.com/product-detail/en/rohm-semiconductor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
15 | R11,R19,R20,R21,R29,R10,R2,R1,R3,R28 | R_0603_1608Metric_Pad1.05x0.95mm_HandSolder | 5.1k | RE0603FRE071KL | 13-RE0603FRE071KLCT-ND | Digikey | 10 | 0.1 | 1 | https://www.digikey.com/en/products/detail/yageo/RE0603FRE07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
16 | Q10,Q8,Q7,Q6,Q5,Q4,Q3,Q1,Q2,Q9 | LFPAK56_MOSFET | Q_NMOS_DGS | TL3305AF160QG | EG5350CT-ND | Digikey | 10 | 0.18 | 1.7999999999999998 | https://www.digikey.com/product-detail/en/e-switch/TL3305AF1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
17 | D7,D18,D16,D15,D14,D13,D12,D3,D5,D6,D4,D17 | LED_0603_1608Metric_Pad1.05x0.95mm_HandSolder | LED | OS102011MA1QN1 | CKN9559-ND | Digikey | 12 | 0.48 | 5.76 | https://www.digikey.com/products/en?keywords=C%26K%20OS102011MA1QN1
18 | C12,C21,C22,C23,C28,C11,C6,C5,C7,C27 | C_0603_1608Metric_Pad1.05x0.95mm_HandSolder | 0.1uF | OKI-78SR-3.3/1.5-W36H-C | 811-3014-ND | Digikey | 10 | 4.3 | 43 | https://www.digikey.com/product-detail/en/murata-power-solut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
19 | D2,D1 | D_0603_1608Metric_Pad1.05x0.95mm_HandSolder | D |  |  |  | 2
20 | C4,C3,C2,C1 | CP_Radial_D12.5mm_P5.00mm | 470uF |  |  |  | 4
21 | Conn12 | Anderson_2_Horizontal_Stacked | Spare |  |  |  | 1
22 | Conn11 | Anderson_2_Horizontal_Stacked | Auxiliary |  |  |  | 1
23 | Conn8 | Anderson_2_Horizontal_Stacked | Vaccum |  |  |  | 1
24 | Conn4 | Anderson_2_Horizontal_Stacked | 12 V |  |  |  | 1
25 | Conn3 | Anderson_2_Horizontal_Stacked | Motor 2 |  |  |  | 1
26 | Conn2 | Anderson_2_Horizontal_Stacked | Rockets |  |  |  | 1
27 | F7 | ATC_Fuse_Block | 10 |  |  |  | 1
28 | F8 | ATC_Fuse_Block | 15 |  |  |  | 1
29 | GND1 | BATT_PWR_VIA | Via |  |  |  | 1
30 | J3V1,J5V1 | TestPoint_Pad_2.5x2.5mm | Test_Point |  |  |  | 2
31 | R17 | R_0603_1608Metric_Pad1.05x0.95mm_HandSolder | 510 |  |  |  | 1
32 | R18 | R_0603_1608Metric_Pad1.05x0.95mm_HandSolder | 330 |  |  |  | 1
33 | R25 | R_0603_1608Metric_Pad1.05x0.95mm_HandSolder | 1200 |  |  |  | 1
34 | V1 | BATT_PWR_VIA | BATT_PWR_VIA |  |  |  | 1
35 | Conn7 | Anderson_2_Horizontal_Stacked | Motor 3 |  |  |  | 1
36 | Conn1 | Anderson_2_Horizontal_Stacked | Motor 1 |  |  |  | 1
37 | Conn9 | Anderson_2_Horizontal_Stacked | Motor 4 |  |  |  | 1
38 | Conn10 | Anderson_2_Horizontal_Stacked | Driveboard |  |  |  | 1
